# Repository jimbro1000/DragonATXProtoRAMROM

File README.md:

# Dragon 32 ATX Prototype RAM and ROM

This repository contains the KiCad project files
to produce the RAM and ROM component board for my
ATX Prototype backplane.

This design requires the ATX backplane board in order 
to operate
See https://github.com/jimbro1000/DragonATXProto

## Notes

Revision 1 of the board contains a design using 
conventional DRAM, either 64k or 256k. Revision 2 will 
use SRAM.

Revision 3 will contain just a Flash ROM for use with
the FPGA board on the backplane as this carries a
large volume of RAM onboard.

This design has been completed using KiCad 9. Earlier
versions of KiCad are not compatible.

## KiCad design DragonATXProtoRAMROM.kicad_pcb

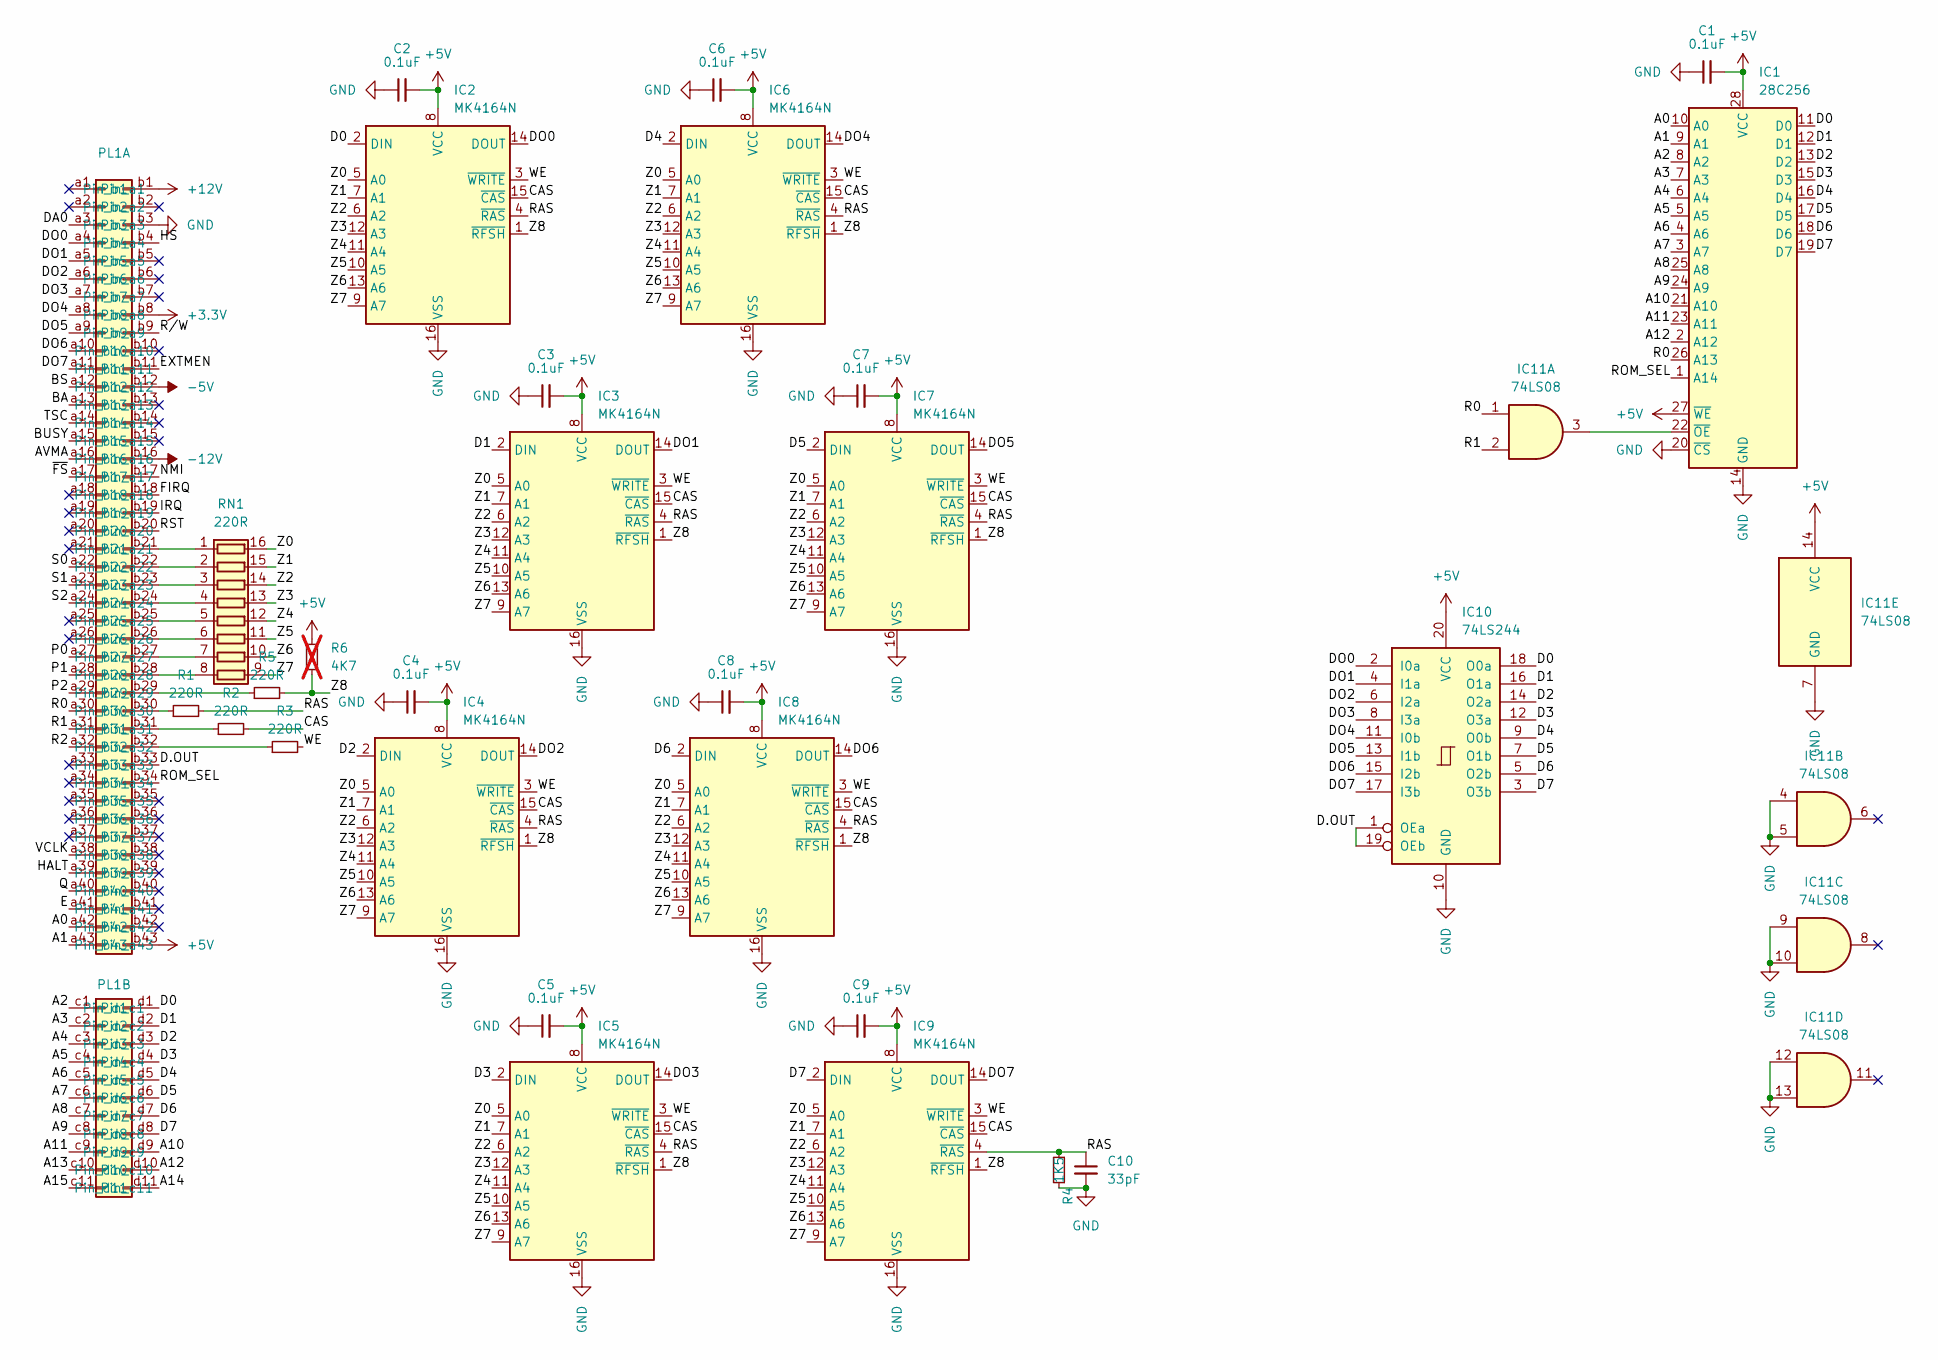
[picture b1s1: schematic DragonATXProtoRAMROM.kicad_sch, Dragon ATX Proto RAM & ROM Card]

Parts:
C1, C2, C3, C4, C5, C6, C7, C8, C9: 0.1uF; C_Disc_D4.3mm_W1.9mm_P5.00mm; DigiKey BC1101CT-ND
C10: 33pF; C_Disc_D3.0mm_W2.0mm_P2.50mm; DigiKey BC1007CT-ND
IC1: 28C256; DIP-28_W15.24mm
IC2, IC3, IC4, IC5, IC6, IC7, IC8, IC9: MK4164N; DIP-16_W7.62mm
IC10: 74LS244; DIP-20_W7.62mm
IC11: 74LS08; DIP-14_W7.62mm
PL1: Card_Edge
R1, R2, R3, R5: 220R; R_Axial_DIN0204_L3.6mm_D1.6mm_P2.54mm_Vertical
R4: 1K5; R_Axial_DIN0204_L3.6mm_D1.6mm_P2.54mm_Vertical; DigiKey CF14JT1K50CT-ND
R6: 4K7; R_Axial_DIN0204_L3.6mm_D1.6mm_P2.54mm_Vertical; not fitted
RN1: 220R; DIP-16_W7.62mm

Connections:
+3.3V: PL1.b8
+5V: C1.2, C2.2, C3.2, C4.2, C5.2, C6.2, C7.2, C8.2, C9.2, IC1.27 (~WE), IC1.28 (VCC), IC2.8 (VCC), IC3.8 (VCC), IC4.8 (VCC), IC5.8 (VCC), IC6.8 (VCC), IC7.8 (VCC), IC8.8 (VCC), IC9.8 (VCC), IC10.20 (VCC), IC11.14 (VCC), PL1.b43, R6.2
+12V: PL1.b1
-5V: PL1.b12
-12V: PL1.b16
/A0: IC1.10 (A0), PL1.a42
/A1: IC1.9 (A1), PL1.a43
/A2: IC1.8 (A2), PL1.c1
/A3: IC1.7 (A3), PL1.c2
/A4: IC1.6 (A4), PL1.c3
/A5: IC1.5 (A5), PL1.c4
/A6: IC1.4 (A6), PL1.c5
/A7: IC1.3 (A7), PL1.c6
/A8: IC1.25 (A8), PL1.c7
/A9: IC1.24 (A9), PL1.c8
/A10: IC1.21 (A10), PL1.d9
/A11: IC1.23 (A11), PL1.c9
/A12: IC1.2 (A12), PL1.d10
/A13: PL1.c10
/A14: PL1.d11
/A15: PL1.c11
/AVMA: PL1.a16
/BA: PL1.a13
/BS: PL1.a12
/BUSY: PL1.a15
/CAS: IC2.15 (~CAS), IC3.15 (~CAS), IC4.15 (~CAS), IC5.15 (~CAS), IC6.15 (~CAS), IC7.15 (~CAS), IC8.15 (~CAS), IC9.15 (~CAS), R2.2
/D0: IC1.11 (D0), IC2.2 (DIN), IC10.18 (O0a), PL1.d1
/D1: IC1.12 (D1), IC3.2 (DIN), IC10.16 (O1a), PL1.d2
/D2: IC1.13 (D2), IC4.2 (DIN), IC10.14 (O2a), PL1.d3
/D3: IC1.15 (D3), IC5.2 (DIN), IC10.12 (O3a), PL1.d4
/D4: IC1.16 (D4), IC6.2 (DIN), IC10.9 (O0b), PL1.d5
/D5: IC1.17 (D5), IC7.2 (DIN), IC10.7 (O1b), PL1.d6
/D6: IC1.18 (D6), IC8.2 (DIN), IC10.5 (O2b), PL1.d7
/D7: IC1.19 (D7), IC9.2 (DIN), IC10.3 (O3b), PL1.d8
/D.OUT: IC10.1 (OEa), IC10.19 (OEb), PL1.b33
/DA0: PL1.a3
/DO0: IC2.14 (DOUT), IC10.2 (I0a), PL1.a4
/DO1: IC3.14 (DOUT), IC10.4 (I1a), PL1.a5
/DO2: IC4.14 (DOUT), IC10.6 (I2a), PL1.a6
/DO3: IC5.14 (DOUT), IC10.8 (I3a), PL1.a7
/DO4: IC6.14 (DOUT), IC10.11 (I0b), PL1.a8
/DO5: IC7.14 (DOUT), IC10.13 (I1b), PL1.a9
/DO6: IC8.14 (DOUT), IC10.15 (I2b), PL1.a10
/DO7: IC9.14 (DOUT), IC10.17 (I3b), PL1.a11
/E: PL1.a41
/EXTMEN: PL1.b11
/FIRQ: PL1.b18
/HALT: PL1.a39
/HS: PL1.b4
/IRQ: PL1.b19
/NMI: PL1.b17
/P0: PL1.a27
/P1: PL1.a28
/P2: PL1.a29
/Q: PL1.a40
/R0: IC1.26 (A13), IC11.1, PL1.a30
/R1: IC11.2, PL1.a31
/R2: PL1.a32
/RAS: C10.1, IC2.4 (~RAS), IC3.4 (~RAS), IC4.4 (~RAS), IC5.4 (~RAS), IC6.4 (~RAS), IC7.4 (~RAS), IC8.4 (~RAS), IC9.4 (~RAS), R1.2, R4.2
/ROM_SEL: IC1.1 (A14), PL1.b34
/RST: PL1.b20
/R/W: PL1.b9
/S0: PL1.a22
/S1: PL1.a23
/S2: PL1.a24
/TSC: PL1.a14
/VCLK: PL1.a38
/WE: IC2.3 (~WRITE), IC3.3 (~WRITE), IC4.3 (~WRITE), IC5.3 (~WRITE), IC6.3 (~WRITE), IC7.3 (~WRITE), IC8.3 (~WRITE), IC9.3 (~WRITE), R3.2
/Z0: IC2.5 (A0), IC3.5 (A0), IC4.5 (A0), IC5.5 (A0), IC6.5 (A0), IC7.5 (A0), IC8.5 (A0), IC9.5 (A0), RN1.16 (R1.2)
/Z1: IC2.7 (A1), IC3.7 (A1), IC4.7 (A1), IC5.7 (A1), IC6.7 (A1), IC7.7 (A1), IC8.7 (A1), IC9.7 (A1), RN1.15 (R2.2)
/Z2: IC2.6 (A2), IC3.6 (A2), IC4.6 (A2), IC5.6 (A2), IC6.6 (A2), IC7.6 (A2), IC8.6 (A2), IC9.6 (A2), RN1.14 (R3.2)
/Z3: IC2.12 (A3), IC3.12 (A3), IC4.12 (A3), IC5.12 (A3), IC6.12 (A3), IC7.12 (A3), IC8.12 (A3), IC9.12 (A3), RN1.13 (R4.2)
/Z4: IC2.11 (A4), IC3.11 (A4), IC4.11 (A4), IC5.11 (A4), IC6.11 (A4), IC7.11 (A4), IC8.11 (A4), IC9.11 (A4), RN1.12 (R5.2)
/Z5: IC2.10 (A5), IC3.10 (A5), IC4.10 (A5), IC5.10 (A5), IC6.10 (A5), IC7.10 (A5), IC8.10 (A5), IC9.10 (A5), RN1.11 (R6.2)
/Z6: IC2.13 (A6), IC3.13 (A6), IC4.13 (A6), IC5.13 (A6), IC6.13 (A6), IC7.13 (A6), IC8.13 (A6), IC9.13 (A6), RN1.10 (R7.2)
/Z7: IC2.9 (A7), IC3.9 (A7), IC4.9 (A7), IC5.9 (A7), IC6.9 (A7), IC7.9 (A7), IC8.9 (A7), IC9.9 (A7), RN1.9 (R8.2)
/Z8: IC2.1 (~RFSH), IC3.1 (~RFSH), IC4.1 (~RFSH), IC5.1 (~RFSH), IC6.1 (~RFSH), IC7.1 (~RFSH), IC8.1 (~RFSH), IC9.1 (~RFSH), R5.2, R6.1
/~FS: PL1.a17
GND: C1.1, C2.1, C3.1, C4.1, C5.1, C6.1, C7.1, C8.1, C9.1, C10.2, IC1.14 (GND), IC1.20 (~CS), IC2.16 (VSS), IC3.16 (VSS), IC4.16 (VSS), IC5.16 (VSS), IC6.16 (VSS), IC7.16 (VSS), IC8.16 (VSS), IC9.16 (VSS), IC10.10 (GND), IC11.4, IC11.5, IC11.7 (GND), IC11.9, IC11.10, IC11.12, IC11.13, PL1.b3, R4.1
unnamed: IC1.22 (~OE), IC11.3
unnamed: PL1.b21, RN1.1 (R1.1)
unnamed: PL1.b22, RN1.2 (R2.1)
unnamed: PL1.b23, RN1.3 (R3.1)
unnamed: PL1.b24, RN1.4 (R4.1)
unnamed: PL1.b25, RN1.5 (R5.1)
unnamed: PL1.b26, RN1.6 (R6.1)
unnamed: PL1.b27, RN1.7 (R7.1)
unnamed: PL1.b28, RN1.8 (R8.1)
unnamed: PL1.b29, R5.1
unnamed: PL1.b30, R1.1
unnamed: PL1.b31, R2.1
unnamed: PL1.b32, R3.1

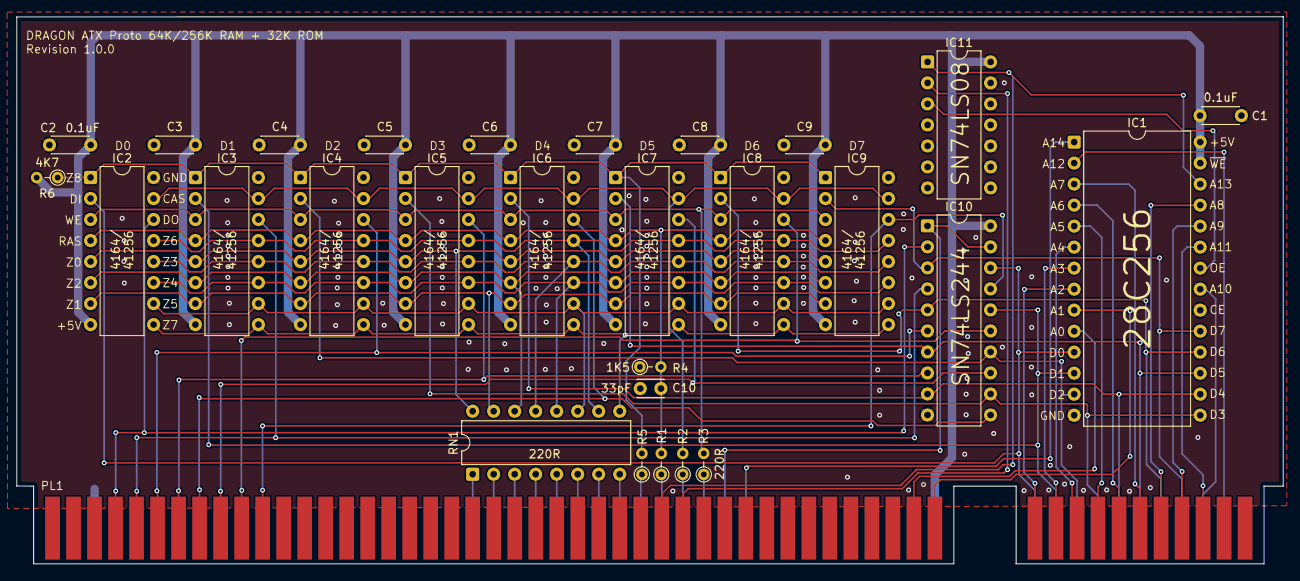
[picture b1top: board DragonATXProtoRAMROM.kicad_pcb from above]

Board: 2 copper layers, 153.1 x 66.1 mm, 29 parts (0 on the bottom side), 60 nets.

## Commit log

2025-03-17 update card edge spec
2025-03-24 fix missing gnd pin connection
